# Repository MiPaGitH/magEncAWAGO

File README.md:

# magEncAWAGO
interface for AWAGO magnetic encoder (configuration and data acquisition)
includes also PCB design (with AWAGO AEAT6600) done in KiCad
TODO - add option at runtime to switch from config mode to data mode
TODO - code cleanup

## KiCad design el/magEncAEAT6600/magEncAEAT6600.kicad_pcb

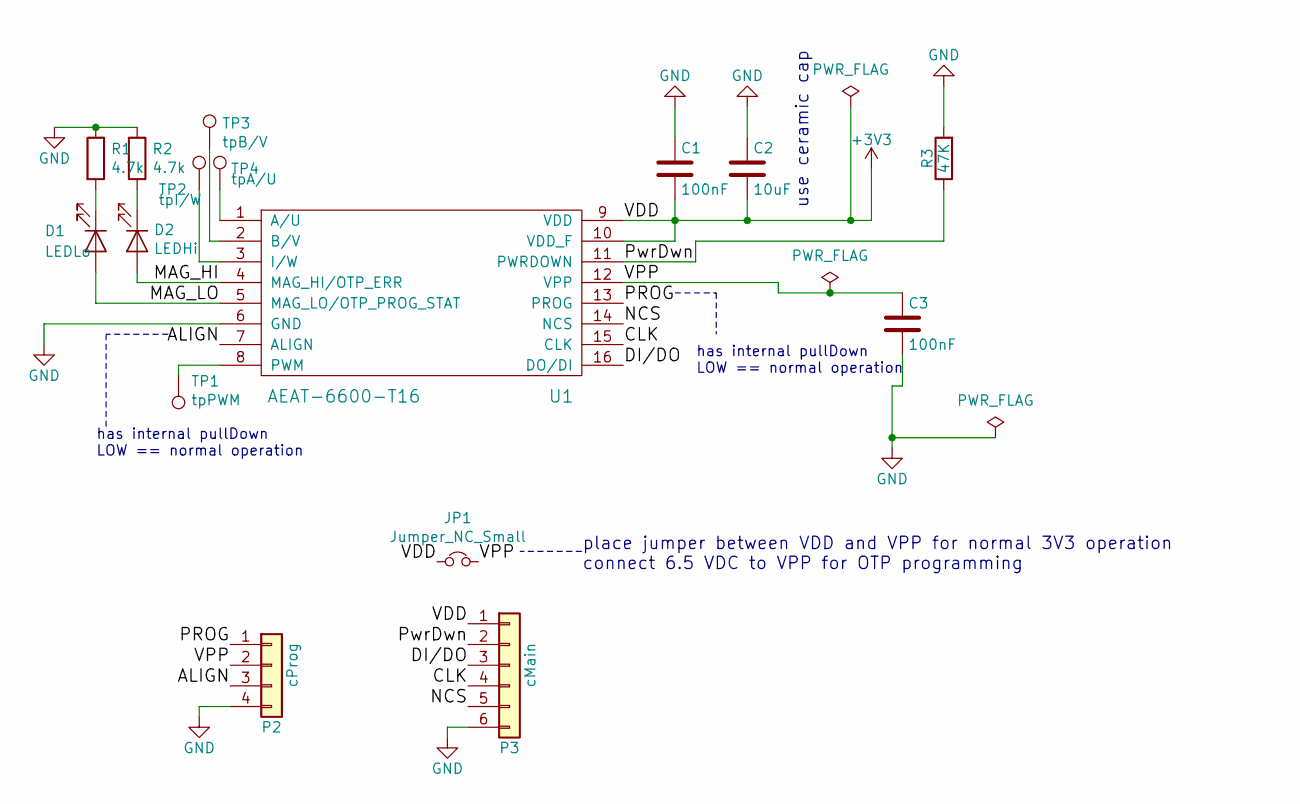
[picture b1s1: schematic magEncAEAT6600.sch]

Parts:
C1, C3: 100nF; C_1206_3216Metric_Pad1.42x1.75mm_HandSolder
C2: 10uF; C_1210_3225Metric_Pad1.42x2.65mm_HandSolder
D1: LEDLo; LED_1206_3216Metric_Pad1.42x1.75mm_HandSolder
D2: LEDHi; LED_1206_3216Metric_Pad1.42x1.75mm_HandSolder
JP1: Jumper_NC_Small; SolderJumper-2_P1.3mm_Open_TrianglePad1.0x1.5mm
P2: cProg; PinHeader_1x04_P2.54mm_Vertical
P3: cMain; PinHeader_1x06_P2.54mm_Vertical
R1, R2: 4.7k; R_1206_3216Metric_Pad1.42x1.75mm_HandSolder
R3: 47K; R_1206_3216Metric_Pad1.42x1.75mm_HandSolder
TP1: tpPWM; TestPoint_THTPad_D1.0mm_Drill0.5mm
TP2: tpI/W; TestPoint_THTPad_D1.0mm_Drill0.5mm
TP3: tpB/V; TestPoint_THTPad_D1.0mm_Drill0.5mm
TP4: tpA/U; TestPoint_THTPad_D1.0mm_Drill0.5mm
U1: AEAT-6600-T16; TSSOP-16_4.4x5mm_P0.65mm

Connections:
+3V3: C1.2, C2.2, JP1.1, P3.1, U1.9 (VDD), U1.10 (VDD_F)
/ALIGN: P2.3, U1.7 (ALIGN)
/CLK: P3.4, U1.15 (CLK)
/DI/DO: P3.3, U1.16 (DO/DI)
/MAG_HI: D2.2 (A), U1.4 (MAG_HI/OTP_ERR)
/MAG_LO: D1.2 (A), U1.5 (MAG_LO/OTP_PROG_STAT)
/NCS: P3.5, U1.14 (NCS)
/PROG: P2.1, U1.13 (PROG)
/PwrDwn: P3.2, R3.1, U1.11 (PWRDOWN)
/VPP: C3.1, JP1.2, P2.2, U1.12 (VPP)
GND: C1.1, C2.1, C3.2, P2.4, P3.6, R1.1, R2.1, R3.2, U1.6 (GND)
unnamed: D1.1 (K), R1.2
unnamed: D2.1 (K), R2.2
unnamed: TP1.1, U1.8 (PWM)
unnamed: TP2.1, U1.3 (I/W)
unnamed: TP3.1, U1.2 (B/V)
unnamed: TP4.1, U1.1 (A/U)

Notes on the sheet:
use ceramic cap
place jumper between VDD and VPP for normal 3V3 operation connect 6.5 VDC to VPP for OTP programming
has internal pullDown LOW == normal operation

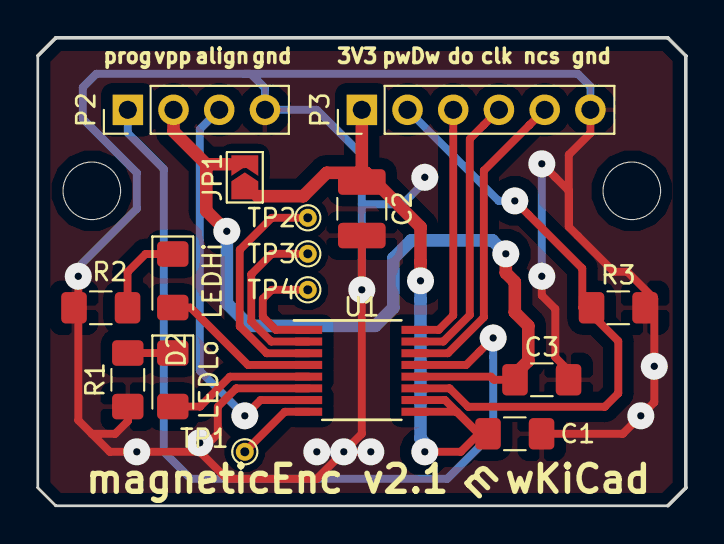
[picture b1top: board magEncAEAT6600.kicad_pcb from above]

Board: 2 copper layers, 36.0 x 26.0 mm, 18 parts (0 on the bottom side), 17 nets.

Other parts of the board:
1, 2: MountingHole_3.2mm_M3

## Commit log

2025-04-05 pcb design tested successfully; initial sw version (see TODO's)
2025-04-06 added uart menu; uart com tested with putty
2025-04-18 added code to process the RX SSI data of encoder value
2025-05-17 added VPP and PROG pins; menu handling updated
2025-06-07 uart commands management updated (using HAL_UARTEx_ReceiveToIdle_DMA)
2025-06-09 fix menu processing; now is shown correctly
2025-07-06 menu commands display corrected; added simple schematic of NucleoF303ZE
2025-07-13 bug fixes to menu processing and so command; now all commands work correctly
